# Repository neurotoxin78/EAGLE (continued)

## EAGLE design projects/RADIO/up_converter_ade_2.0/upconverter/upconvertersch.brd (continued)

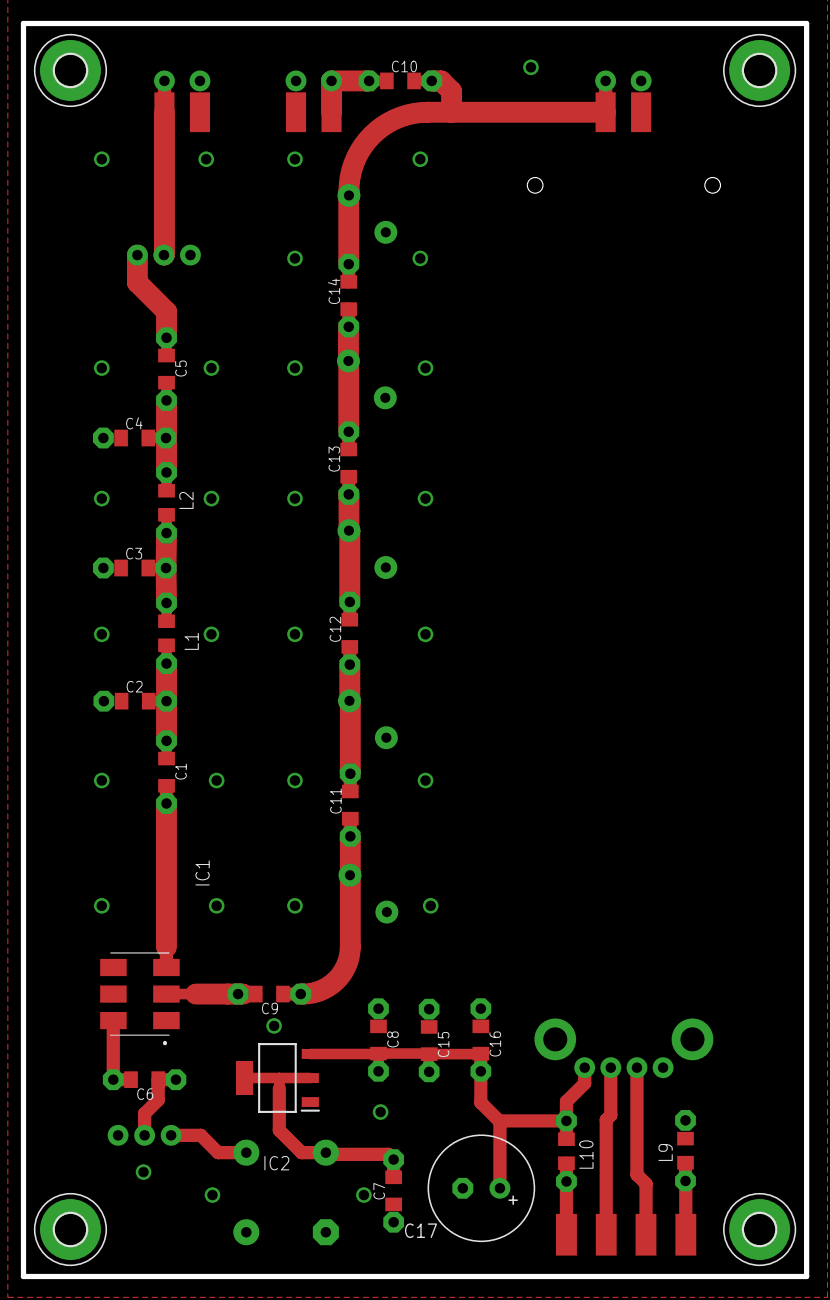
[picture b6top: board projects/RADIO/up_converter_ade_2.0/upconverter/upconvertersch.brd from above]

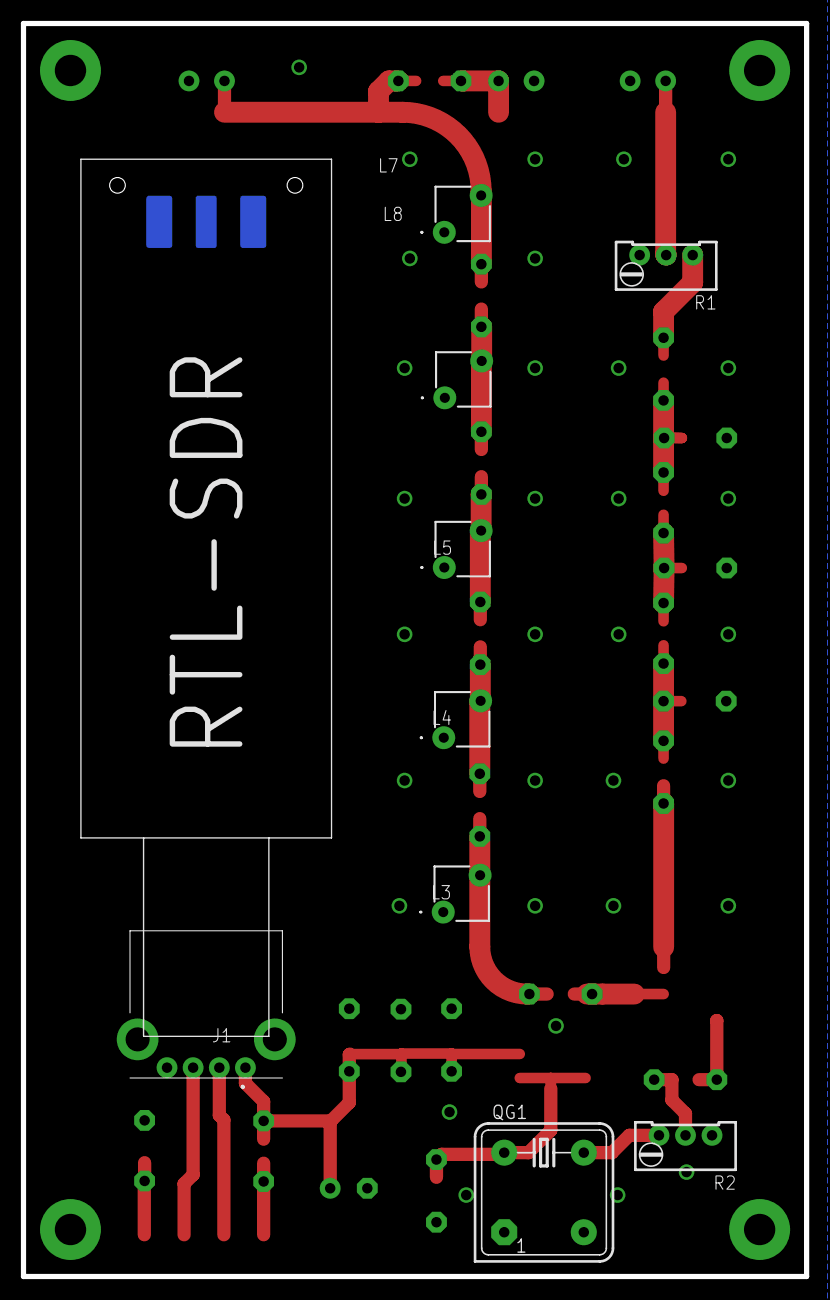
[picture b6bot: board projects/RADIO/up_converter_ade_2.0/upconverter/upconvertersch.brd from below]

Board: 2 copper layers, 75.0 x 120.0 mm, 41 parts (9 on the bottom side), 23 nets.

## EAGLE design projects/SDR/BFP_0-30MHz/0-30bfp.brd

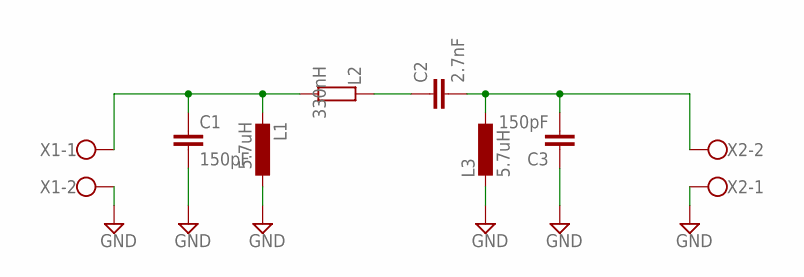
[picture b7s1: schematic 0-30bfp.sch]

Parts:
C1, C3: 150pF; C1206K
C2: 2.7nF; C1206K
L1, L3: 5.7uH; 0207/7
L2: 330nH; R1206
X1, X2: W237-102

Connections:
GND: C1.2, C3.1, L1.1, L3.2, X1.2, X2.1
unnamed: C1.1, L1.2, L2.2, X1.1
unnamed: C2.1, L2.1
unnamed: C2.2, C3.2, L3.1, X2.2

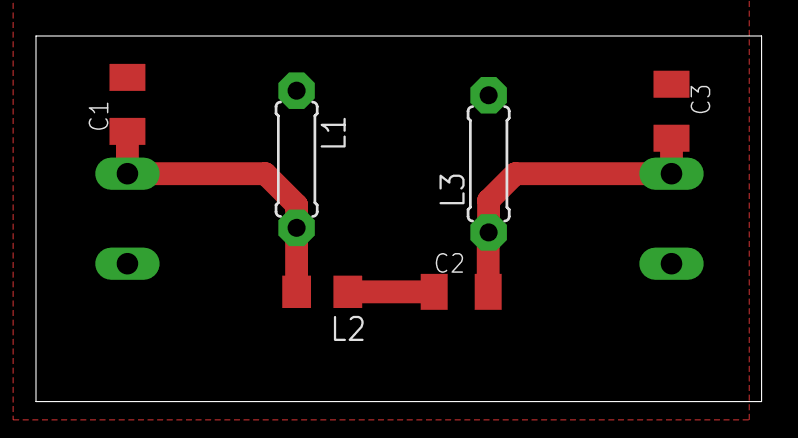
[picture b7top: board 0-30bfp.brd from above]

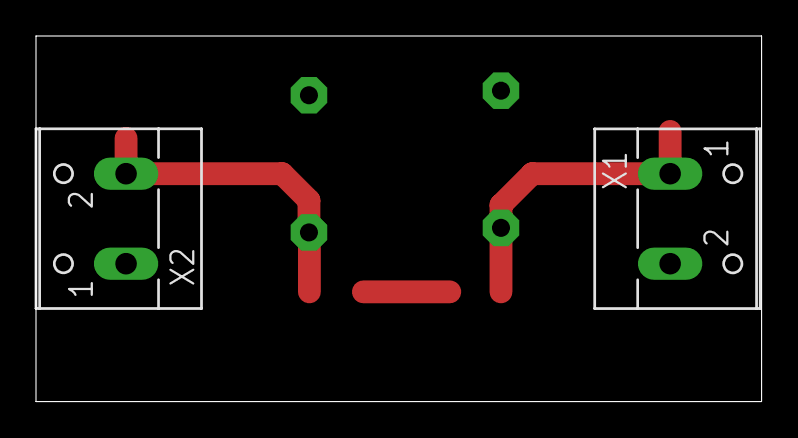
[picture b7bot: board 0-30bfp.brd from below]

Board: 2 copper layers, 40.3 x 20.3 mm, 8 parts (2 on the bottom side), 4 nets.
